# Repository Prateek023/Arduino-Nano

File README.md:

# Custom-Arduino-Nano
This project revolves around a custom-designed Arduino Nano, engineered to meet specific needs. Whether it's for a particular application, compactness, or additional features, this custom Arduino Nano offers a tailored solution for your project requirements.
## Hardware Setup
Assemble the custom-designed Arduino Nano board according to the provided schematic and layout diagrams. Ensure all components are soldered correctly and connections are secure.
## Contributing
Contributions to the Custom Arduino Nano project are welcome! If you'd like to contribute, please follow these guidelines:

  1) Fork the repository and create a new branch for your feature or bug fix.
  2) Make your changes and ensure that the code follows the project's coding conventions.
  3) Test your changes thoroughly.
  4) Submit a pull request with a clear description of your changes and their purpose.

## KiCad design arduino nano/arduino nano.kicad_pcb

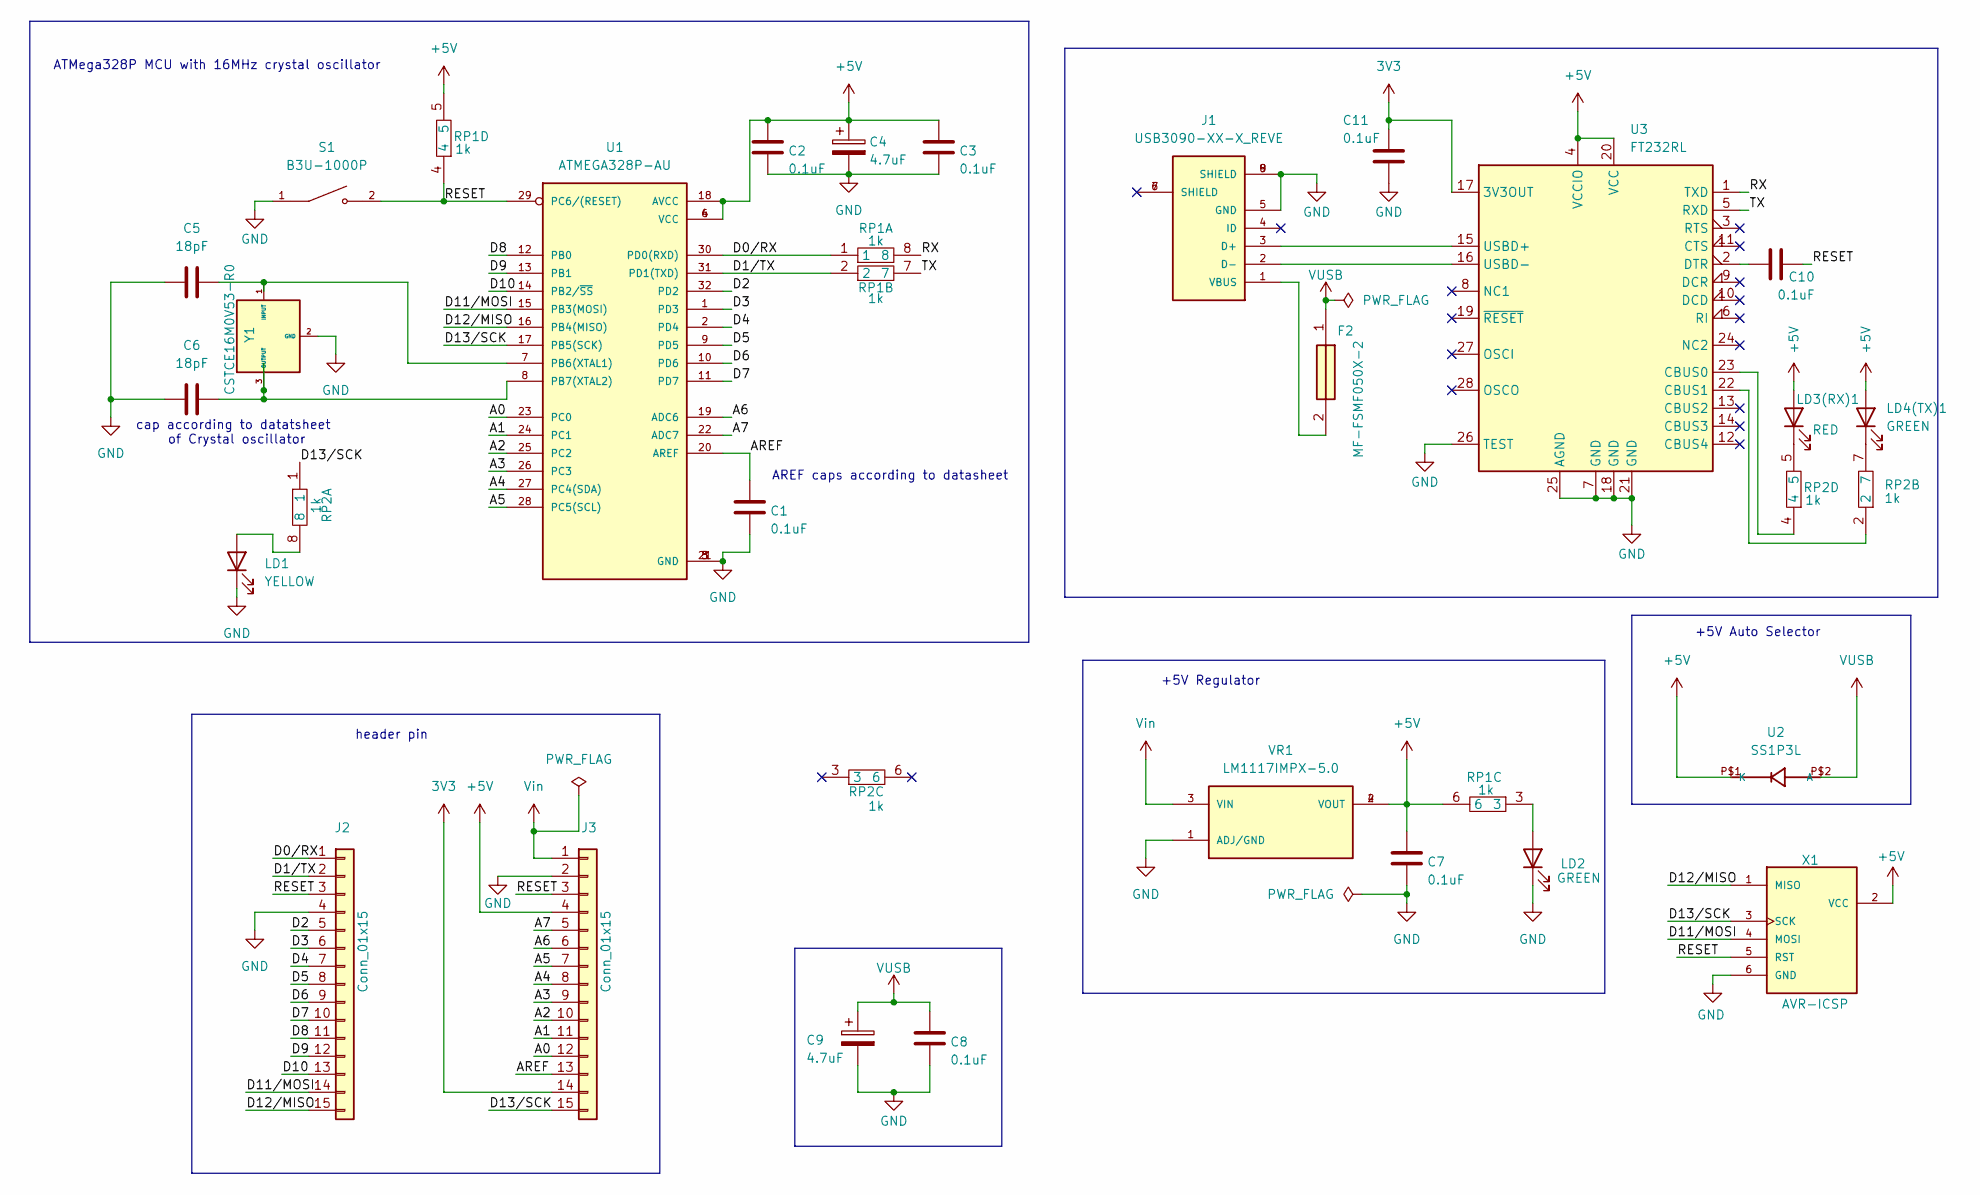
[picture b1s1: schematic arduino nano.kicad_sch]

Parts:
C1, C2, C3, C7, C8, C10, C11: 0.1uF; CAPC2012X94N
C4, C9: 4.7uF; CAPC1608X90N
C5, C6: 18pF; C0805
F2: MF-FSMF050X-2; FUSC1608X100N; Mouser Part Number 652-MFFSMF050X-2
J1: USB3090-XX-X_REVE; GCT_USB3090-XX-X_REVE
J2, J3: Conn_01x15; header_pin1x15
LD1: YELLOW; LEDC2012X50N
LD2: GREEN; LEDC2012X85N
LD3(RX)1: RED; LEDC2012X85N
LD4(TX)1: GREEN; LEDC2012X50N
RP1, RP2: 1k; RESCAXE80P320X160X70-8N
S1: B3U-1000P; SW_B3U-1000P
U1: ATMEGA328P-AU; QFP80P900X900X120-32N; PARTREV 8271A
U2: SS1P3L; DO220AAL
U3: FT232RL; SSOP-28_5.3x10.2mm_P0.65mm
VR1: LM1117IMPX-5.0; SOT230P700X180-4N; PARTREV O
X1: AVR-ICSP; ICSP-2X03-2.54
Y1: CSTCE16M0V53-R0; CSTCE16M0V53R0; Mouser Part Number 81-CSTCE16M0V53-R0

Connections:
3V3: C11.1, J3.14, U3.17 (3V3OUT)
+5V: C2.1, C3.1, C4.1, C7.1, J3.4, LD3(RX)1.2 (A), LD4(TX)1.2 (A), RP1.5, RP1.6, U1.4 (VCC), U1.6 (VCC), U1.18 (AVCC), U2.P$1 (K), U3.4 (VCCIO), U3.20 (VCC), VR1.2 (VOUT), VR1.4 (VOUT), X1.2 (VCC)
/A0: J3.12, U1.23 (PC0)
/A1: J3.11, U1.24 (PC1)
/A2: J3.10, U1.25 (PC2)
/A3: J3.9, U1.26 (PC3)
/A4: J3.8, U1.27 (PC4(SDA))
/A5: J3.7, U1.28 (PC5(SCL))
/A6: J3.6, U1.19 (ADC6)
/A7: J3.5, U1.22 (ADC7)
/AREF: C1.1, J3.13, U1.20 (AREF)
/D0/RX: J2.1, RP1.1, U1.30 (PD0(RXD))
/D1/TX: J2.2, RP1.2, U1.31 (PD1(TXD))
/D2: J2.5, U1.32 (PD2)
/D3: J2.6, U1.1 (PD3)
/D4: J2.7, U1.2 (PD4)
/D5: J2.8, U1.9 (PD5)
/D6: J2.9, U1.10 (PD6)
/D7: J2.10, U1.11 (PD7)
/D8: J2.11, U1.12 (PB0)
/D9: J2.12, U1.13 (PB1)
/D10: J2.13, U1.14 (PB2/~SS)
/D11/MOSI: J2.14, U1.15 (PB3(MOSI)), X1.4 (MOSI)
/D12/MISO: J2.15, U1.16 (PB4(MISO)), X1.1 (MISO)
/D13/SCK: J3.15, RP2.1, U1.17 (PB5(SCK)), X1.3 (SCK)
/RESET: C10.2, J2.3, J3.3, RP1.4, S1.2, U1.29 (PC6/(RESET)), X1.5 (RST)
/RX: RP1.8, U3.1 (TXD)
/TX: RP1.7, U3.5 (RXD)
GND: C1.2, C2.2, C3.2, C4.2, C5.1, C6.1, C7.2, C8.2, C9.2, C11.2, J1.5 (GND), J1.8 (SHIELD), J1.9 (SHIELD), J2.4, J3.2, LD1.1 (K), LD2.1 (K), S1.1, U1.3 (GND), U1.5 (GND), U1.21 (GND), U3.7 (GND), U3.18 (GND), U3.21 (GND), U3.25 (AGND), U3.26 (TEST), VR1.1 (ADJ/GND), X1.6 (GND), Y1.2 (GND)
unnamed: J1.3 (D+), U3.15 (USBD+)
unnamed: J1.2 (D-), U3.16 (USBD-)
unnamed: F2.2, J1.1 (VBUS)
unnamed: LD1.2 (A), RP2.8
unnamed: LD2.2 (A), RP1.3
unnamed: LD3(RX)1.1 (K), RP2.5
unnamed: LD4(TX)1.1 (K), RP2.7
unnamed: C5.2, U1.7 (PB6(XTAL1)), Y1.1 (INPUT)
unnamed: C6.2, U1.8 (PB7(XTAL2)), Y1.3 (OUTPUT)
unnamed: RP2.4, U3.23 (CBUS0)
unnamed: RP2.2, U3.22 (CBUS1)
unnamed: C10.1, U3.2 (DTR)
VUSB: C8.1, C9.1, F2.1, U2.P$2 (A)
Vin: J3.1, VR1.3 (VIN)

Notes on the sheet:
ATMega328P MCU with 16MHz crystal oscillator
AREF caps according to datasheet
+5V Auto Selector
cap according to datatsheet of Crystal oscillator
+5V Regulator
header pin

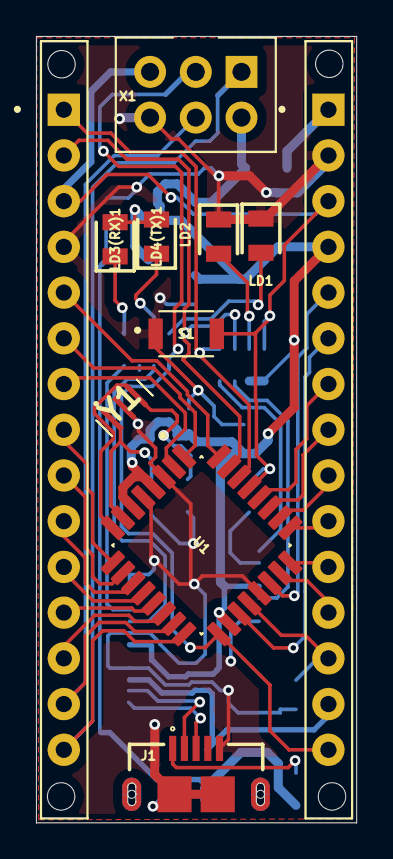
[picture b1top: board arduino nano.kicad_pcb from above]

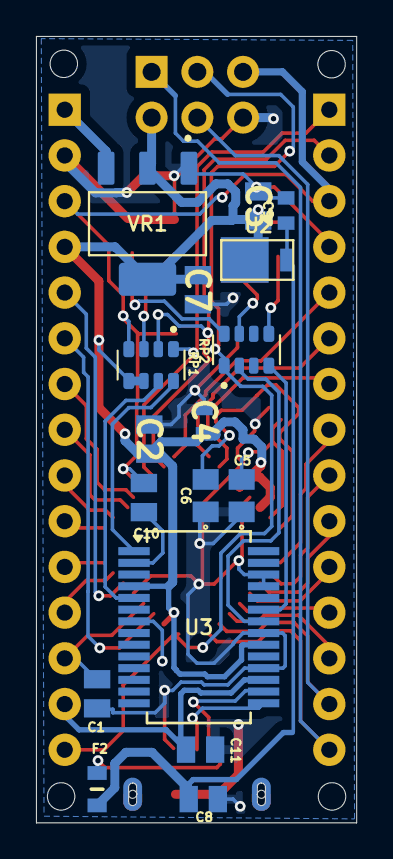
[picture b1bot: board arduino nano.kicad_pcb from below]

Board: 2 copper layers, 17.8 x 43.7 mm, 28 parts (17 on the bottom side), 43 nets.

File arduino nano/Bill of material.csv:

Reference,Value,Datasheet,Footprint,Qty,DNP
"C1,C2,C3,C7,C8,C10,C11",0.1uF,https://www.mouser.in/datasheet/2/40/KGM_X7R-3223212.pdf,cap_0.1uF:CAPC2012X94N,7,
"C4,C9",4.7uF,https://www.mouser.in/datasheet/2/281/murata_03052018_GRM_Se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,cap_4.7uF_16V:CAPC1608X90N,2,
"C5,C6",18pF,https://www.mouser.in/datasheet/2/447/KEM_C1003_C0G_SMD-3316496.pdf,cap_18pF:C0805,2,
F2,MF-FSMF050X-2,https://www.mouser.in/datasheet/2/54/mffsmf-777670.pdf,KiCad:FUSC1608X100N,1,
J1,USB3090-XX-X_REVE,https://www.snapeda.com/parts/USB3090-30-A/Global%20Connecto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,USB3090-XX-X_REVE:GCT_USB3090-XX-X_REVE,1,
"J2,J3",Conn_01x15,https://cdn.amphenol-cs.com/media/wysiwyg/files/documentatio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,my_Library:header_pin1x15,2,
LD1,YELLOW,~,LED_orange:LEDC2012X50N,1,
"LD2,LD4(TX)1",GREEN,https://www.mouser.in/datasheet/2/216/APHCM2012CGCK_F01-34366.pdf,-- mixed values --,2,
LD3(RX)1,RED,https://www.mouser.in/datasheet/2/216/APT2012SRCPRV-56885.pdf,LED_red:LEDC2012X85N,1,
"RP1,RP2",1k,https://www.yageo.com/upload/media/product/app/datasheet/rch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,YC164_JR_071KL:RESCAXE80P320X160X70-8N,2,
S1,B3U-1000P,https://omronfs.omron.com/en_US/ecb/products/pdf/en-b3u.pdf,B3U_1000P:SW_B3U-1000P,1,
U1,ATMEGA328P-AU,https://ww1.microchip.com/downloads/aemDocuments/documents/M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,ATMEGA328P-AU:QFP80P900X900X120-32N,1,
U2,SS1P3L,https://www.vishay.com/docs/88915/ss1p3l.pdf,SS1P3L:DO220AAL,1,
U3,FT232RL,https://www.ftdichip.com/Support/Documents/DataSheets/ICs/DS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,Package_SO:SSOP-28_5.3x10.2mm_P0.65mm,1,
VR1,LM1117IMPX-5.0,https://www.ti.com/lit/ds/symlink/lm1117.pdf?HQS=dis-mous-nu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,LM1117IMPX-5.0:SOT230P700X180-4N,1,
X1,AVR-ICSP,,AVR-ICSP:ICSP-2X03-2.54,1,
Y1,CSTCE16M0V53-R0,https://www.murata.com/en-sg/products/productdetail?partno=C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,crystal_3Terminal:CSTCE16M0V53R0,1,
